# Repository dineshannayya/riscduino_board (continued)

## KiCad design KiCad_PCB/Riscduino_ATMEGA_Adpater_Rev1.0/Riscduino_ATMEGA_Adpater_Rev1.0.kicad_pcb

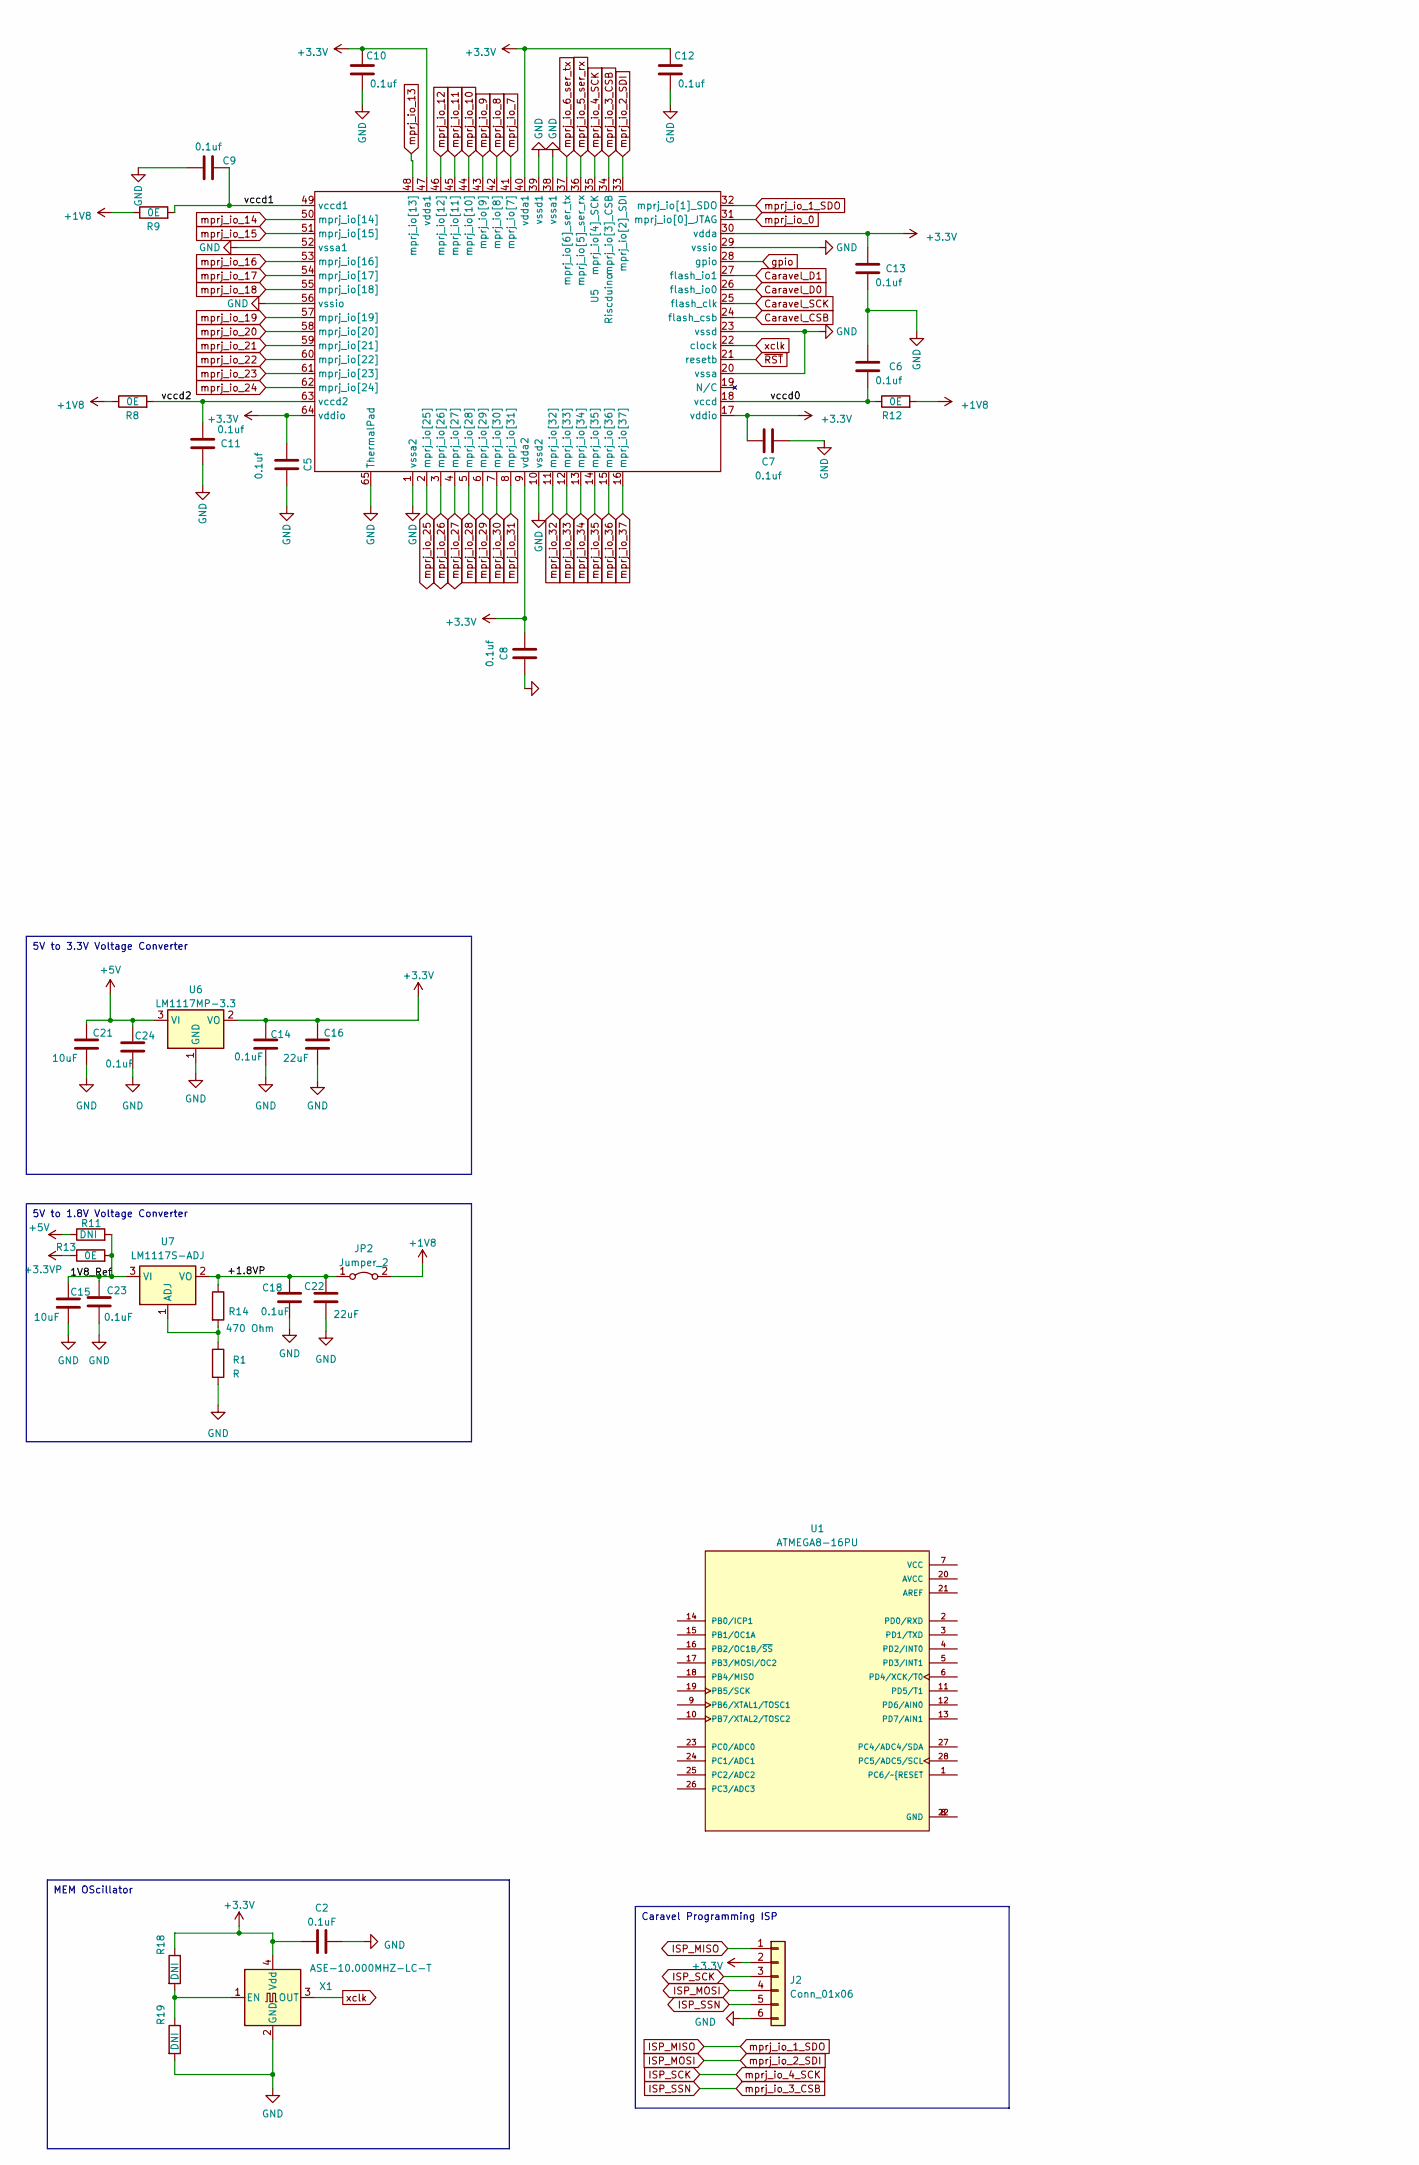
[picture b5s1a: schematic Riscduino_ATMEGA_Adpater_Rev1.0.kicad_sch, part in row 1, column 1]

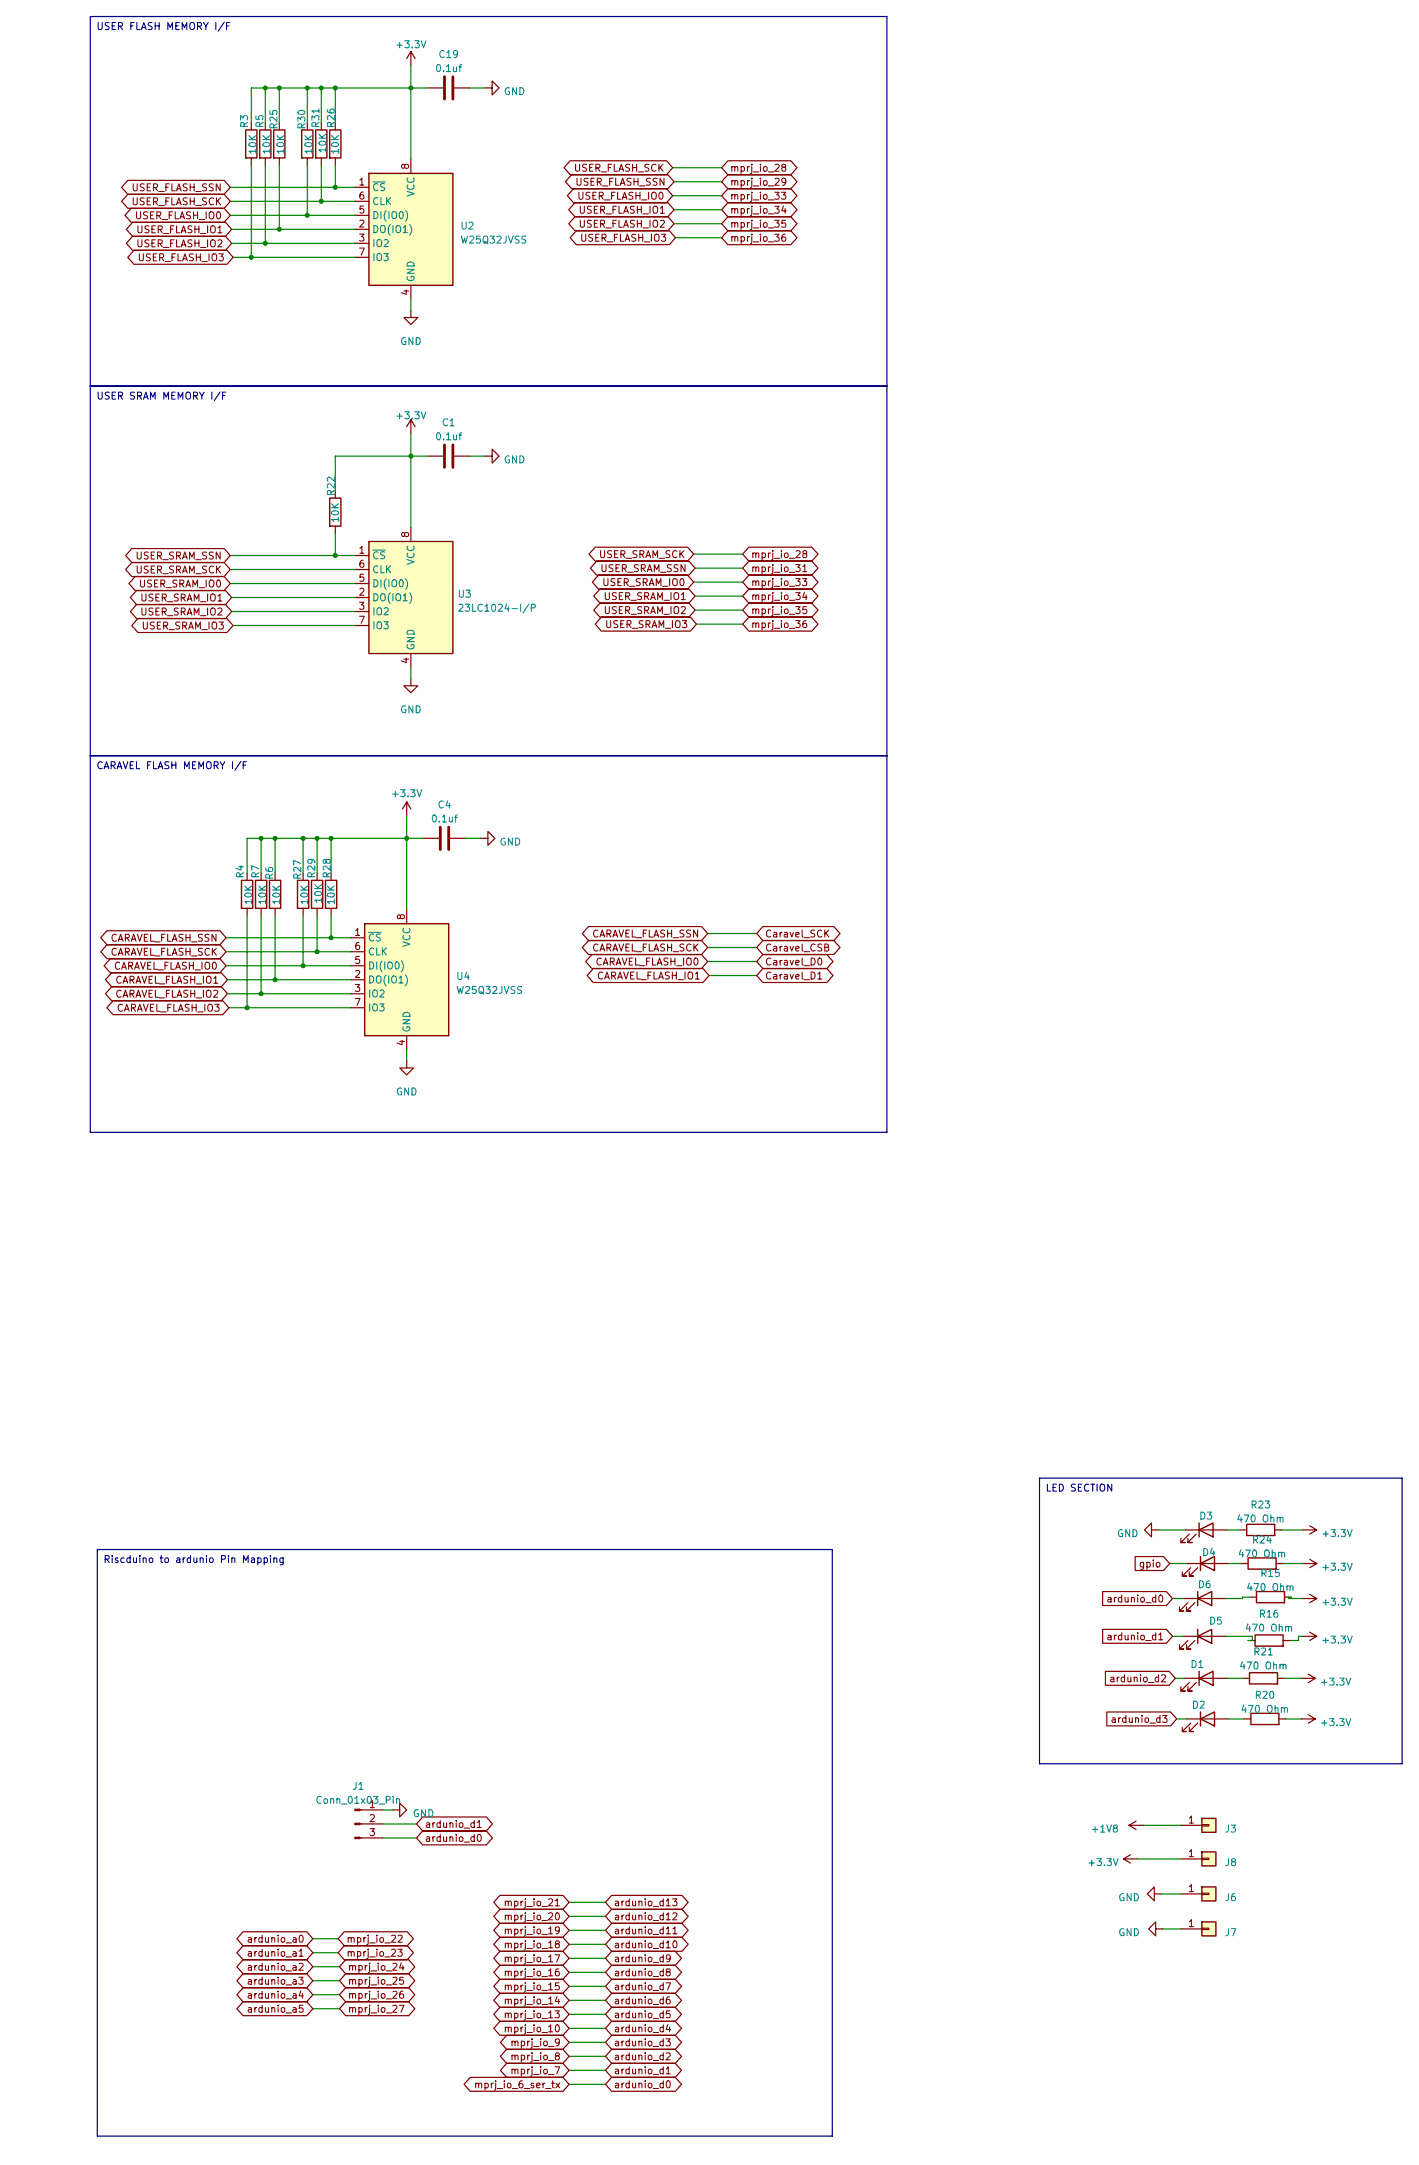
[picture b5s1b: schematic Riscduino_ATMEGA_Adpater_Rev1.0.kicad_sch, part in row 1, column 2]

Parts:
C1, C4, C5, C6, C7, C8, C9, C10, C11, C12, C13, C19: 0.1uf; C_0603_1608Metric_Pad1.08x0.95mm_HandSolder
C2, C14, C18, C23, C24: 0.1uF; C_0603_1608Metric_Pad1.08x0.95mm_HandSolder
C15, C21: 10uF; C_0805_2012Metric_Pad1.18x1.45mm_HandSolder
C16, C22: 22uF; C_0805_2012Metric_Pad1.18x1.45mm_HandSolder
D1, D2, D4, D5: GREEN LED; LED_0805_2012Metric_Pad1.15x1.40mm_HandSolder
D3: RED LED; LED_0805_2012Metric_Pad1.15x1.40mm_HandSolder
D6: BLUE LED; LED_0805_2012Metric_Pad1.15x1.40mm_HandSolder
J1: Conn_01x03_Pin; PinHeader_1x03_P2.54mm_Vertical
J2: Conn_01x06; PinHeader_1x06_P2.54mm_Vertical
J3, J6, J7, J8: Conn_01x01; PinHeader_1x01_P2.54mm_Vertical
JP2: Jumper_2; PinHeader_1x02_P2.54mm_Vertical
R1: R; R_1206_3216Metric_Pad1.30x1.75mm_HandSolder
R3, R4, R5, R6, R7, R22, R25, R26, R27, R28, R29, R30, R31: 10K; R_0603_1608Metric_Pad0.98x0.95mm_HandSolder
R8, R9, R12, R13: 0E; R_0603_1608Metric_Pad0.98x0.95mm_HandSolder
R11, R18, R19: DNI; R_0603_1608Metric_Pad0.98x0.95mm_HandSolder
R14: 470 Ohm; R_1206_3216Metric_Pad1.30x1.75mm_HandSolder
R15, R16, R20, R21, R23, R24: 470 Ohm; R_0603_1608Metric_Pad0.98x0.95mm_HandSolder
U1: ATMEGA8-16PU; ATMEG8_28Pin_Jumper; PARTREV 2486R- 07/07
U2, U4: W25Q32JVSS; SOIC-8_5.23x5.23mm_P1.27mm
U3: 23LC1024-I/P; DIP-8_W7.62mm_LongPads
U5: Riscduino; RISCDUINO_QFN-64-1EP_9x9mm_P0.5mm_EP7.65x7.65mm_Ver1.1
U6: LM1117MP-3.3; SOT-223-3_TabPin2
U7: LM1117S-ADJ; SOT-223-3_TabPin2
X1: ASE-10.000MHZ-LC-T; Crystal_SMD_Abracon_ABM8G-4Pin_3.2x2.5mm

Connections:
+1V8: J3.1, JP2.2 (B), R8.1, R9.1, R12.2
+5V: C21.1, C24.1, R11.1, U6.3 (VI)
/+1.8VP: C18.1, C22.1, JP2.1 (A), R14.1, U7.2 (VO)
/vccd0: C6.2, R12.1, U5.18 (vccd)
/vccd1: C9.2, R9.2, U5.49 (vccd1)
/vccd2: C11.1, R8.2, U5.63 (vccd2)
CARAVEL_FLASH_IO0: R27.2, U4.5 (DI(IO0)), U5.26 (flash_io0)
CARAVEL_FLASH_IO1: R6.2, U4.2 (DO(IO1)), U5.27 (flash_io1)
CARAVEL_FLASH_IO2: R7.2, U4.3 (IO2)
CARAVEL_FLASH_IO3: R4.2, U4.7 (IO3)
CARAVEL_FLASH_SCK: R29.2, U4.6 (CLK), U5.24 (flash_csb)
CARAVEL_FLASH_SSN: R28.2, U4.1 (~CS), U5.25 (flash_clk)
GND: C1.2, C2.2, C4.2, C5.1, C6.1, C7.1, C8.1, C9.1, C10.2, C11.2, C12.2, C13.2, C14.2, C15.2, C16.2, C18.2, C19.2, C21.2, C22.2, C23.2, C24.2, D3.1 (K), J1.1, J2.6, J6.1, J7.1, R1.2, R19.2, U2.4 (GND), U3.4 (GND), U4.4 (GND), U5.1 (vssa2), U5.10 (vssd2), U5.20 (vssa), U5.23 (vssd), U5.29 (vssio), U5.38 (vssa1), U5.39 (vssd1), U5.52 (vssa1), U5.56 (vssio), U5.65 (ThermalPad), U6.1 (GND), X1.2 (GND)
ISP_MISO: J2.1, U5.32 (mprj_io[1]_SDO)
ISP_MOSI: J2.4, U5.33 (mprj_io[2]_SDI)
ISP_SCK: J2.3, U5.35 (mprj_io[4]_SCK)
ISP_SSN: J2.5, U5.34 (mprj_io[3]_CSB)
unnamed: D1.2 (A), R21.1
unnamed 18: D2.2 (A), R20.1; also elsewhere on the board
unnamed: D3.2 (A), R23.1
unnamed: D4.2 (A), R24.1
unnamed: D5.2 (A), R16.1
unnamed: D6.2 (A), R15.1
unnamed: U1.8 (GND), U1.22 (GND)
unnamed: R1.1, R14.2, U7.1 (ADJ)
unnamed: C15.1, C23.1, R11.2, R13.2, U7.3 (VI)
unnamed: R18.2, R19.1, X1.1 (EN)
USER_FLASH_IO0: R30.2, U2.5 (DI(IO0)), U3.5 (DI(IO0)), U5.12 (mprj_io[33])
USER_FLASH_IO1: R25.2, U2.2 (DO(IO1)), U3.2 (DO(IO1)), U5.13 (mprj_io[34])
USER_FLASH_IO2: R5.2, U2.3 (IO2), U3.3 (IO2), U5.14 (mprj_io[35])
USER_FLASH_IO3: R3.2, U2.7 (IO3), U3.7 (IO3), U5.15 (mprj_io[36])
USER_FLASH_SCK: R31.2, U2.6 (CLK), U3.6 (CLK), U5.5 (mprj_io[28])
USER_FLASH_SSN: R26.2, U2.1 (~CS), U5.6 (mprj_io[29])
USER_SRAM_SSN: R22.2, U3.1 (~CS), U5.8 (mprj_io[31])
ardunio_a0: U5.60 (mprj_io[22])
ardunio_a1: U5.61 (mprj_io[23])
ardunio_a2: U5.62 (mprj_io[24])
ardunio_a3: U5.2 (mprj_io[25])
ardunio_a4: U5.3 (mprj_io[26])
ardunio_a5: U5.4 (mprj_io[27])
ardunio_d0: D6.1 (K), J1.3, U5.37 (mprj_io[6]_ser_tx)
ardunio_d1: D5.1 (K), J1.2, U5.41 (mprj_io[7])
ardunio_d2: D1.1 (K), U5.42 (mprj_io[8])
ardunio_d3: D2.1 (K), U5.43 (mprj_io[9]); also elsewhere on the board
ardunio_d4: U5.44 (mprj_io[10])
ardunio_d5: U5.48 (mprj_io[13])
ardunio_d6: U5.50 (mprj_io[14])
ardunio_d7: U5.51 (mprj_io[15])
ardunio_d8: U5.53 (mprj_io[16])
ardunio_d9: U5.54 (mprj_io[17])
ardunio_d10: U5.55 (mprj_io[18])
ardunio_d11: U5.57 (mprj_io[19])
ardunio_d12: U5.58 (mprj_io[20])
ardunio_d13: U5.59 (mprj_io[21])
gpio: D4.1 (K), U5.28 (gpio)
mprj_io_0: U5.31 (mprj_io[0]_JTAG)
mprj_io_5_ser_rx: U5.36 (mprj_io[5]_ser_rx)
mprj_io_11: U5.45 (mprj_io[11])
mprj_io_12: U5.46 (mprj_io[12])
mprj_io_30: U5.7 (mprj_io[30])
mprj_io_32: U5.11 (mprj_io[32])
mprj_io_37: U5.16 (mprj_io[37])
xclk: U5.22 (clock), X1.3 (OUT)
~RST: U5.21 (resetb)

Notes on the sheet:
MEM OScillator
5V to 3.3V Voltage Converter
LED SECTION
Riscduino to ardunio Pin Mapping
USER SRAM MEMORY I/F
Caravel Programming ISP
USER FLASH MEMORY I/F
5V to 1.8V Voltage Converter
CARAVEL FLASH MEMORY I/F

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
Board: 2 copper layers, 71 parts (19 on the bottom side), 42 nets, no tracks yet.

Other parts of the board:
JP1: Jumper_2; PinHeader_1x02_P2.54mm_Vertical
locked: GREEN LED; LED_0805_2012Metric_Pad1.15x1.40mm_HandSolder

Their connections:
unnamed 18: locked.2 (A); also elsewhere on the board
ardunio_d3: locked.1 (K); also elsewhere on the board

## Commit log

2023-07-25 KiCad PCB
2023-07-25 ver 1.1 boards
2023-07-25 gerber files
2023-07-27 Riscduino Uno 1.2
2023-07-27 Riscduino Adpater Used in MPW-2 Debug
2023-07-30 Kicad Foot Prints
2023-07-30 atmega adapter
2023-08-01 BOM Update
2023-08-01 BOM Addition
2023-08-12 Rev Uno 1.2 update
2023-08-13 Riscduino Uno Rev1.2
2023-08-13 Library
2023-08-14 PCB Update
2023-08-23 Uno 1.2
2023-08-29 Uno 1.1.3
2023-08-29 Removed Backup
2023-08-30 Riscduino Test Ver 1.0
2023-09-07 Power Supervisory Circuit
2023-09-08 1.3 Uno Schematic update
2023-09-16 Riscduino Uno 1.3
2023-12-24 Debug 1.3 Update
2023-12-25 Debug 1.3 BOM clean up
2023-12-25 Debug PCB View
2023-12-26 component tracking xls update
2024-02-03 Debug Board 1.4
2024-02-04 upodate
2024-02-21 Application Note
2024-03-04 Riscduino FPGA Setup
2024-03-15 Riscduino FPGA 1.1
2024-03-15 Gerber
